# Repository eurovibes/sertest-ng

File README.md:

<!-- SPDX-FileCopyrightText: 2025 Benedikt Spranger <b.spranger@linutronix.de> -->
<!-- SPDX-License-Identifier: CERN-OHL-S-2.0 -->

# sertest-ng - A swiss knife serial testing tool

Serial interfaces like RS-232, RS-422/485 or CAN bus are even used in this
modern times. While reworking the 8250 driver in the Linux kernel jogness
faced plethora of nasty hardware dedication with modern serial hardware.
Single tasks overtop the banks in getting functional hardware. This sucks
and reliable full featured serial testing hardwaare is needed.

sertest-ng tries to fill that gap. It has a USB interface to control a
CAN/CAN-FD bus interface, a full featured RS-232 interface and a RS-422/485
interface. On top a RX/TX only RS-232 is equipped.

## License rules

sertest-ng is provided under the terms of the CERN-OHL-S license version 2 as
provided in the LICENSES/CERN-OHL-S-2.0 file.

Instead of adding license boilerplates to the individual files, sertest-ng uses
SPDX license identifiers, which are machine parseable and considered legaly
equivalent.

The SPDX license identifier in sertest-ng shall be added at the first possible
line in a file which can contain a comment. This is normally the first line
except for scripts. Scripts require the #!PATH_TO_INTERPRETER tag in the
first line; place the SPDX identifier into the second line.

The SPDX license identifier is added in form of a comment.

## Copyright and License
Copyright Benedikt Spranger 2025.
This source describes Open Hardware and is licensed under the CERNOHL-S v2.
You may redistribute and modify this source and make products using it
under the terms of the CERN-OHL-S v2
(https://ohwr.org/cern ohl_s_v2.txt).
This source is distributed WITHOUT ANY EXPRESS OR IMPLIED
WARRANTY, INCLUDING OF MERCHANTABILITY, SATISFACTORY
QUALITY AND FITNESS FOR A PARTICULAR PURPOSE. Please see
the CERN-OHL-S v2 for applicable conditions.
Source location: https://github.com/eurovibes/sertest-ng
As per CERN-OHL-S v2 section 4, should You produce hardware based
on this source, You must where practicable maintain the Source Location
visible on the external case of the sertest-ng or other products you make using
this source.

# Dedication
This hardware is dedicated to the great Linux Kernel Crew at Linutronix (https://www.linutronix.de)

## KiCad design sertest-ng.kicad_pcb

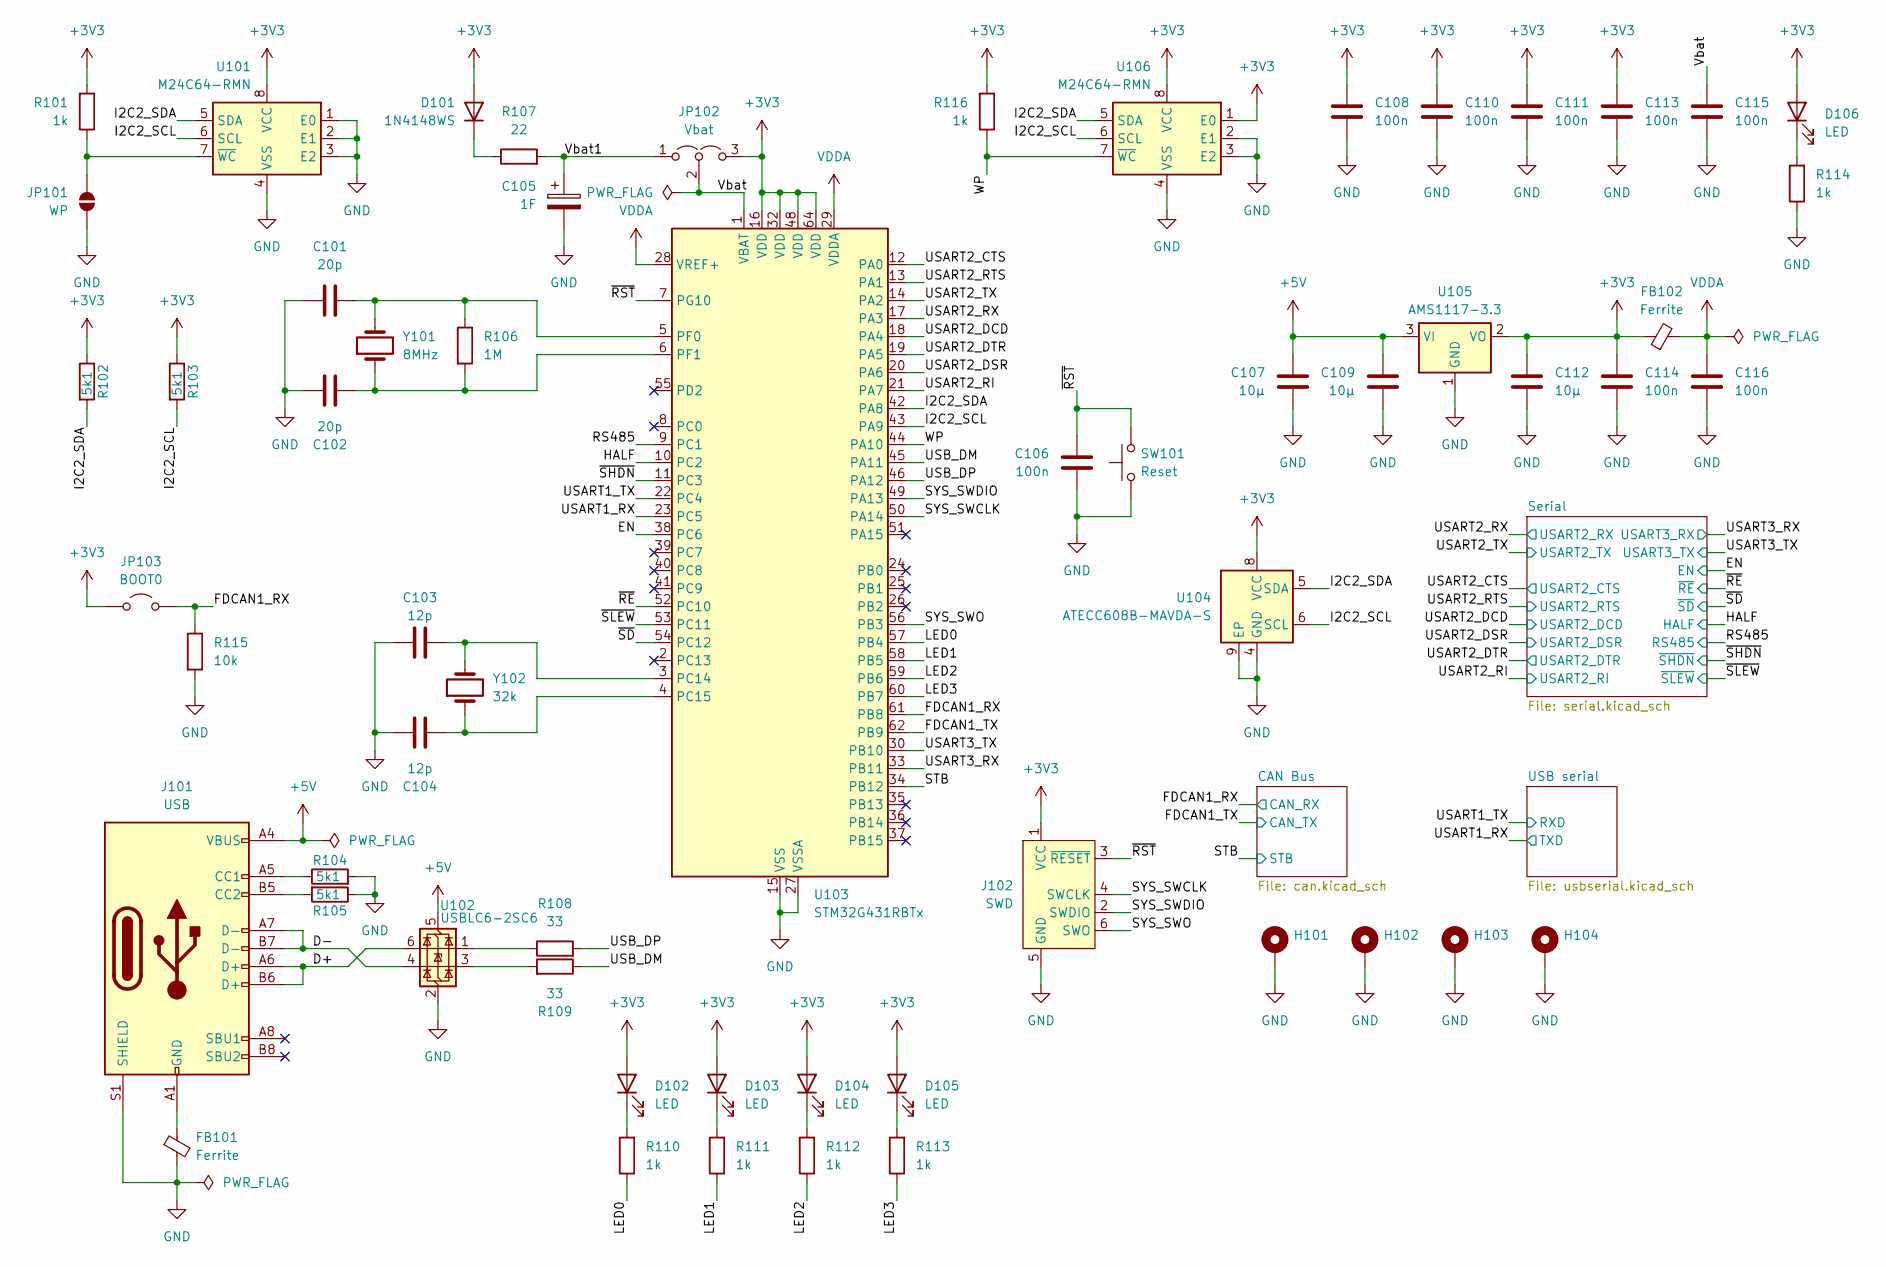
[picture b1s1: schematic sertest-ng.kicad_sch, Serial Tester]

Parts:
C101, C102: 20p; C_0402_1005Metric; lcsc# C1554
C103, C104: 12p; C_0402_1005Metric; lcsc# C1547
C105: 1F; CP_Radial_D8.0mm_P3.50mm
C106: 100n; C_0402_1005Metric; mpn CL05B104KB54PNC; LCSC# C307331
C107, C109, C112: 10µ; C_0805_2012Metric; lcsc# C15850
C108, C110, C111, C113, C114, C115, C116: 100n; C_0402_1005Metric; lcsc# C307331
D101: 1N4148WS; D_SOD-323; lcsc# C2128
D102, D103, D104, D105, D106: LED; LED_0603_1608Metric; mpn KT-0603R; LCSC# C2286
FB101: Ferrite; L_0805_2012Metric; mpn GZ1608D601TF; LCSC# C1002
FB102: Ferrite; L_0805_2012Metric; lcsc# C1015
H101, H102, H103, H104: MountingHole_3.2mm_M3_ISO14580_Pad; mpn N/A
J101: USB; USB_C_Receptacle_G-Switch_GT-USB-7010ASV; lcsc# C2988369
J102: SWD; Tag-Connect_TC2030-IDC-FP_2x03_P1.27mm_Vertical
JP101: WP; SolderJumper-2_P1.3mm_Open_Pad1.0x1.5mm
JP102: Vbat; SolderJumper-3_P1.3mm_Open_Pad1.0x1.5mm
JP103: BOOT0; SolderJumper-2_P1.3mm_Open_Pad1.0x1.5mm
R101, R110, R111, R112, R113, R114, R116: 1k; R_0402_1005Metric; mpn 0402WGF1001TCE; LCSC# C11702
R102, R103, R104, R105: 5k1; R_0402_1005Metric; lcsc# C25905
R106: 1M; R_0402_1005Metric; lcsc# C26083
R107: 22; R_1206_3216Metric; lcsc# C17958
R108, R109: 33; R_0402_1005Metric; lcsc# C25105
R115: 10k; R_0402_1005Metric; lcsc# C25744
SW101: Reset; SW_PUSH_6mm; mpn TACT-65R-F
U101, U106: M24C64-RMN; SOIC-8_3.9x4.9mm_P1.27mm; lcsc# C79988
U102: USBLC6-2SC6; SOT-23-6; mpn USBLC6-2SC6; LCSC# C2827654
U103: STM32G431RBTx; LQFP-64_10x10mm_P0.5mm; lcsc# C431633
U104: ATECC608B-MAVDA-S; DFN-8-1EP_3x2mm_P0.5mm_EP1.3x1.5mm; mpn ATECC608B-MAVDA-S; LCSC# C17350254
U105: AMS1117-3.3; SOT-223-3_TabPin2; lcsc# C6186
Y101: 8MHz; Crystal_SMD_5032-2Pin_5.0x3.2mm; lcsc# C115962
Y102: 32k; Crystal_SMD_3215-2Pin_3.2x1.5mm; lcsc# C32346

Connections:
+3V3: C108.1, C110.1, C111.1, C112.1, C113.1, C114.1, D101.2 (A), D102.2 (A), D103.2 (A), D104.2 (A), D105.2 (A), D106.2 (A), FB102.1, J102.1 (VCC), JP102.3 (B), JP103.1 (A), R101.2, R102.1, R103.1, R116.2, U101.8 (VCC), U103.16 (VDD), U103.32 (VDD), U103.48 (VDD), U103.64 (VDD), U104.8 (VCC), U105.2 (VO), U106.1 (E0), U106.8 (VCC); also elsewhere on the board
+5V: C107.1, C109.1, J101.A4 (VBUS), J101.A9 (VBUS), J101.B4 (VBUS), J101.B9 (VBUS), U102.5 (VBUS), U105.3 (VI)
/D+: J101.A6 (D+), J101.B6 (D+), U102.6 (I/O1)
/D-: J101.A7 (D-), J101.B7 (D-), U102.4 (I/O2)
/EN: U103.38 (PC6); also elsewhere on the board
/FDCAN1_RX: JP103.2 (B), R115.1, U103.61 (PB8); also elsewhere on the board
/FDCAN1_TX: U103.62 (PB9); also elsewhere on the board
/HALF: U103.10 (PC2); also elsewhere on the board
/I2C2_SCL: R103.2, U101.6 (SCL), U103.43 (PA9), U104.6 (SCL), U106.6 (SCL)
/I2C2_SDA: R102.2, U101.5 (SDA), U103.42 (PA8), U104.5 (SDA), U106.5 (SDA)
/LED0: R110.1, U103.57 (PB4)
/LED1: R111.1, U103.58 (PB5)
/LED2: R112.1, U103.59 (PB6)
/LED3: R113.1, U103.60 (PB7)
/RS485: U103.9 (PC1); also elsewhere on the board
/STB: U103.34 (PB12); also elsewhere on the board
/SYS_SWCLK: J102.4 (SWCLK), U103.50 (PA14)
/SYS_SWDIO: J102.2 (SWDIO), U103.49 (PA13)
/SYS_SWO: J102.6 (SWO), U103.56 (PB3)
/USART1_RX: U103.23 (PC5); also elsewhere on the board
/USART1_TX: U103.22 (PC4); also elsewhere on the board
/USART2_CTS: U103.12 (PA0); also elsewhere on the board
/USART2_DCD: U103.18 (PA4); also elsewhere on the board
/USART2_DSR: U103.20 (PA6); also elsewhere on the board
/USART2_DTR: U103.19 (PA5); also elsewhere on the board
/USART2_RI: U103.21 (PA7); also elsewhere on the board
/USART2_RTS: U103.13 (PA1); also elsewhere on the board
/USART2_RX: U103.17 (PA3); also elsewhere on the board
/USART2_TX: U103.14 (PA2); also elsewhere on the board
/USART3_RX: U103.33 (PB11); also elsewhere on the board
/USART3_TX: U103.30 (PB10); also elsewhere on the board
/USB_DM: R109.1, U103.45 (PA11)
/USB_DP: R108.2, U103.46 (PA12)
/Vbat: C115.1, JP102.2 (C), U103.1 (VBAT)
/Vbat1: C105.1, JP102.1 (A), R107.2
/WP: R116.1, U103.44 (PA10), U106.7 (~WC)
/~RE: U103.52 (PC10); also elsewhere on the board
/~RST: C106.1, J102.3 (~RESET), SW101.2, U103.7 (PG10)
/~SD: U103.54 (PC12); also elsewhere on the board
/~SHDN: U103.11 (PC3); also elsewhere on the board
/~SLEW: U103.53 (PC11); also elsewhere on the board
GND: C101.1, C102.1, C103.1, C104.1, C105.2, C106.2, C107.2, C108.2, C109.2, C110.2, C111.2, C112.2, C113.2, C114.2, C115.2, C116.2, FB101.2, H101.1, H102.1, H103.1, H104.1, J101.S1 (SHIELD), J102.5 (GND), JP101.1 (A), R104.2, R105.1, R114.1, R115.2, SW101.1, U101.1 (E0), U101.2 (E1), U101.3 (E2), U101.4 (VSS), U102.2 (GND), U103.15 (VSS), U103.27 (VSSA), U103.31 (VSS), U103.47 (VSS), U103.63 (VSS), U104.4 (GND), U104.9 (EP), U105.1 (GND), U106.2 (E1), U106.3 (E2), U106.4 (VSS); also elsewhere on the board
unnamed: D101.1 (K), R107.1
unnamed: D102.1 (K), R110.2
unnamed: D103.1 (K), R111.2
unnamed: D104.1 (K), R112.2
unnamed: D105.1 (K), R113.2
unnamed: D106.1 (K), R114.2
unnamed: FB101.1, J101.A1 (GND), J101.A12 (GND), J101.B1 (GND), J101.B12 (GND)
unnamed: J101.A5 (CC1), R104.1
unnamed: J101.B5 (CC2), R105.2
unnamed: JP101.2 (B), R101.1, U101.7 (~WC)
unnamed: R108.1, U102.1 (I/O1)
unnamed: R109.2, U102.3 (I/O2)
unnamed: C103.2, U103.3 (PC14), Y102.2
unnamed: C104.2, U103.4 (PC15), Y102.1
unnamed: C101.2, R106.1, U103.5 (PF0), Y101.2
unnamed: C102.2, R106.2, U103.6 (PF1), Y101.1
VDDA: C116.1, FB102.2, U103.28 (VREF+), U103.29 (VDDA)

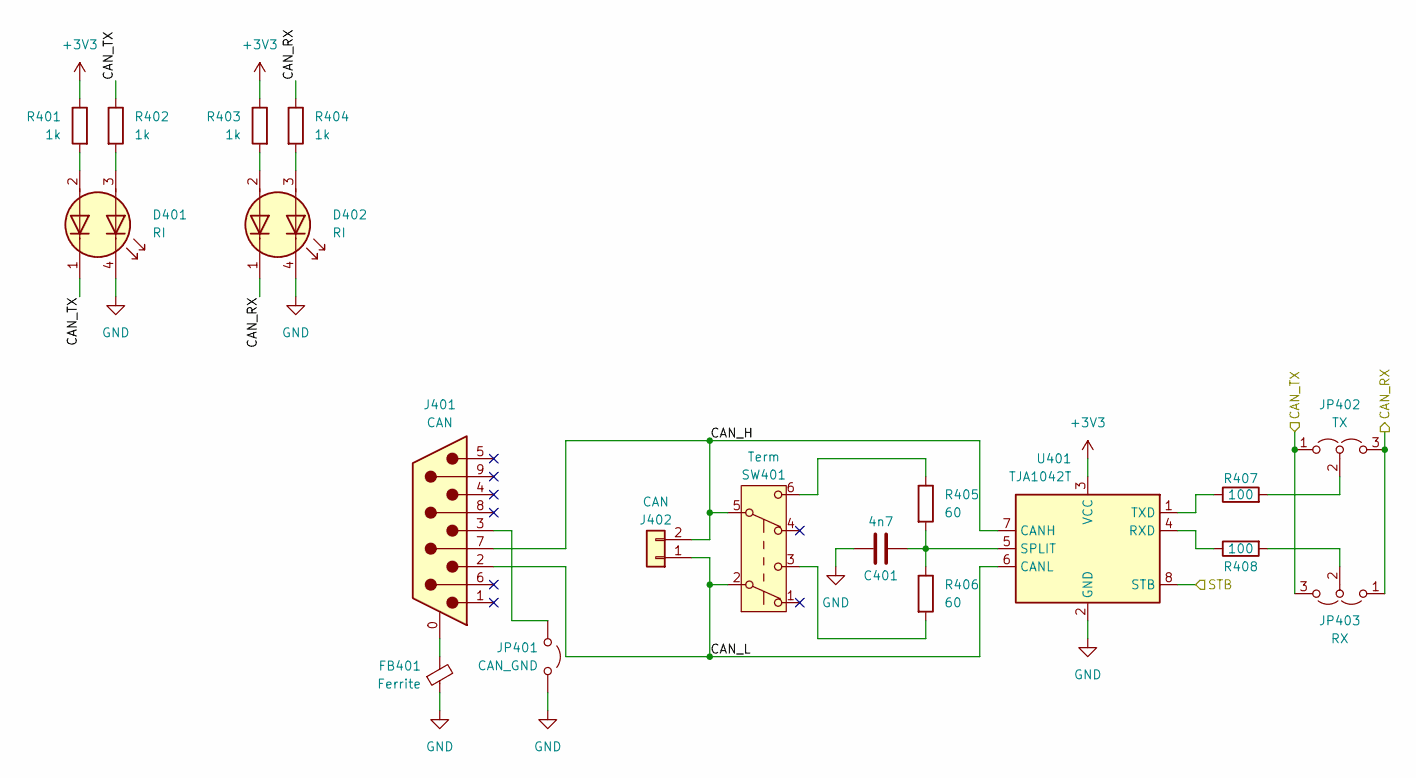
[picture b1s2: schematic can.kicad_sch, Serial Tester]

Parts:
C401: 4n7; C_0402_1005Metric; mpn 0402B472K500NT; LCSC# C1538
D401, D402: RI; LED_Kingbright_AAA3528ESGCT; lcsc# C601701
FB401: Ferrite; L_0805_2012Metric; lcsc# C1015
J401: CAN; DSUB-9_Pins_Horizontal_P2.77x2.84mm_EdgePinOffset4.94mm_Hou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
J402: CAN; TerminalBlock_WAGO_236-402_1x02_P5.00mm_45Degree; mpn 236-402; Digikey# 2946-236-402-ND
JP401: CAN_GND; PinHeader_1x02_P2.54mm_Vertical
JP402: TX; SolderJumper-3_P1.3mm_Open_Pad1.0x1.5mm
JP403: RX; SolderJumper-3_P1.3mm_Open_Pad1.0x1.5mm
R401, R402, R403, R404: 1k; R_0402_1005Metric; lcsc# C11702
R405, R406: 60; R_1206_3216Metric; mpn 1206W4F604JT5E; LCSC# C57572
R407, R408: 100; R_0402_1005Metric; mpn 0402WGF1000TCE; LCSC# C25076
SW401: Term; SW_Push_2P2T_Toggle_CK_PVA2xxH1xxxxxxV2; mpn TL2202EEZB (GRN ACT); Digikey# 141-TL2202EEZB(GRNACT)-ND
U401: TJA1042T; SOIC-8_3.9x4.9mm_P1.27mm; mpn TJA1042T/1J; LCSC# C53670

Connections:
+3V3: R401.1, R403.1, U401.3 (VCC); also elsewhere on the board
/CAN Bus/CAN_H: J401.7, J402.2, SW401.5 (B), U401.7 (CANH)
/CAN Bus/CAN_L: J401.2, J402.1, SW401.2 (B), U401.6 (CANL)
/FDCAN1_RX: D402.1 (K2), JP402.3 (B), JP403.1 (A), R404.1; also elsewhere on the board
/FDCAN1_TX: D401.1 (K2), JP402.1 (A), JP403.3 (B), R402.1; also elsewhere on the board
/STB: U401.8 (STB); also elsewhere on the board
GND: C401.1, D401.4 (K1), D402.4 (K1), FB401.1, JP401.1 (A), U401.2 (GND); also elsewhere on the board
unnamed: D401.3 (A1), R402.2
unnamed: D401.2 (A2), R401.2
unnamed: D402.3 (A1), R404.2
unnamed: D402.2 (A2), R403.2
unnamed: FB401.2, J401.0 (PAD)
unnamed: J401.3, JP401.2 (B)
unnamed: JP402.2 (C), R407.2
unnamed: JP403.2 (C), R408.2
unnamed: R405.1, SW401.6 (C)
unnamed: R406.2, SW401.3 (C)
unnamed: R408.1, U401.4 (RXD)
unnamed: C401.2, R405.2, R406.1, U401.5 (SPLIT)
unnamed: R407.1, U401.1 (TXD)

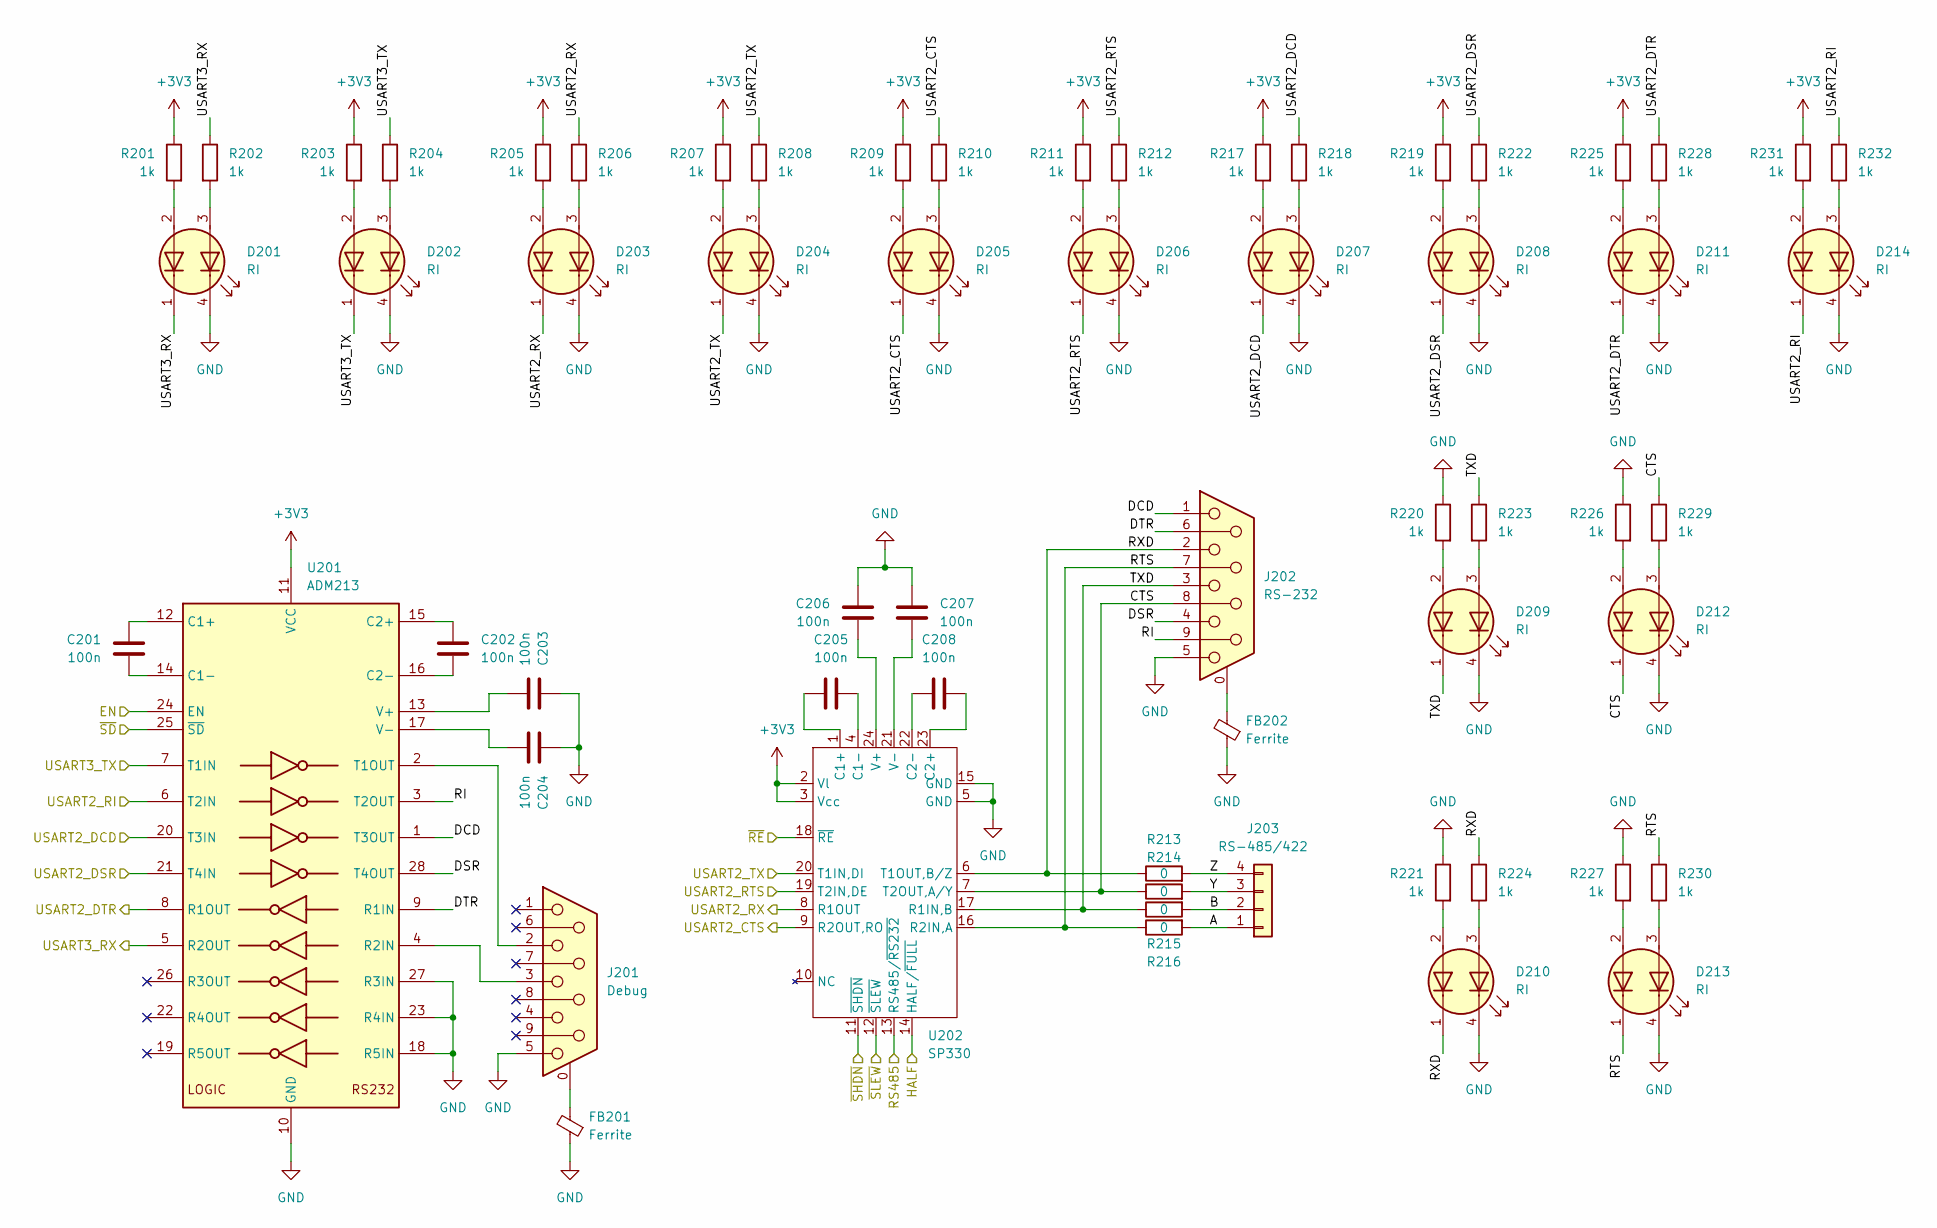
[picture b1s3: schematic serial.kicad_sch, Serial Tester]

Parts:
C201, C202, C203, C204, C205, C206, C207, C208: 100n; C_0402_1005Metric; lcsc# C307331
D201, D202, D203, D204, D205, D206, D207, D208, D209, D210, D211, D212, D213, D214: RI; LED_Kingbright_AAA3528ESGCT; lcsc# C601701
FB201, FB202: Ferrite; L_0805_2012Metric; lcsc# C1015
J201: Debug; DSUB-9_Socket_Horizontal_P2.77x2.84mm_EdgePinOffset4.94mm_H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
J202: RS-232; DSUB-9_Socket_Horizontal_P2.77x2.84mm_EdgePinOffset4.94mm_H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
J203: RS-485/422; TerminalBlock_WAGO_236-404_1x04_P5.00mm_45Degree
R201, R202, R203, R204, R205, R206, R207, R208, R209, R210, R211, R212, R217, R218, R219, R220, R221, R222, R223, R224, R225, R226, R227, R228, R229, R230, R231, R232: 1k; R_0402_1005Metric; lcsc# C11702
R213, R214, R215, R216: 0; R_0402_1005Metric; lcsc# C17168
U201: ADM213; SSOP-28_5.3x10.2mm_P0.65mm; lcsc# C415725
U202: SP330; TSSOP-24_4.4x7.8mm_P0.65mm; lcsc# C916084

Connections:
+3V3: R201.1, R203.1, R205.1, R207.1, R209.1, R211.1, R217.1, R219.1, R225.1, R231.1, U201.11 (VCC), U202.2 (Vl), U202.3 (Vcc); also elsewhere on the board
/EN: U201.24 (EN); also elsewhere on the board
/HALF: U202.14 (HALF/~FULL); also elsewhere on the board
/RS485: U202.13 (RS485/~RS232); also elsewhere on the board
/Serial/A: J203.1, R216.2
/Serial/B: J203.2, R215.2
/Serial/CTS: D212.1 (K2), J202.8, R214.1, R229.1, U202.7 (T2OUT,A/Y)
/Serial/DCD: J202.1, U201.1 (T3OUT)
/Serial/DSR: J202.4, U201.28 (T4OUT)
/Serial/DTR: J202.6, U201.9 (R1IN)
/Serial/RI: J202.9, U201.3 (T2OUT)
/Serial/RTS: D213.1 (K2), J202.7, R216.1, R230.1, U202.16 (R2IN,A)
/Serial/RXD: D210.1 (K2), J202.2, R213.1, R224.1, U202.6 (T1OUT,B/Z)
/Serial/TXD: D209.1 (K2), J202.3, R215.1, R223.1, U202.17 (R1IN,B)
/Serial/Y: J203.3, R214.2
/Serial/Z: J203.4, R213.2
/USART2_CTS: D205.1 (K2), R210.1, U202.9 (R2OUT,RO); also elsewhere on the board
/USART2_DCD: D207.1 (K2), R218.1, U201.20 (T3IN); also elsewhere on the board
/USART2_DSR: D208.1 (K2), R222.1, U201.21 (T4IN); also elsewhere on the board
/USART2_DTR: D211.1 (K2), R228.1, U201.8 (R1OUT); also elsewhere on the board
/USART2_RI: D214.1 (K2), R232.1, U201.6 (T2IN); also elsewhere on the board
/USART2_RTS: D206.1 (K2), R212.1, U202.19 (T2IN,DE); also elsewhere on the board
/USART2_RX: D203.1 (K2), R206.1, U202.8 (R1OUT); also elsewhere on the board
/USART2_TX: D204.1 (K2), R208.1, U202.20 (T1IN,DI); also elsewhere on the board
/USART3_RX: D201.1 (K2), R202.1, U201.5 (R2OUT); also elsewhere on the board
/USART3_TX: D202.1 (K2), R204.1, U201.7 (T1IN); also elsewhere on the board
/~RE: U202.18 (~RE); also elsewhere on the board
/~SD: U201.25 (~SD); also elsewhere on the board
/~SHDN: U202.11 (~SHDN); also elsewhere on the board
/~SLEW: U202.12 (~SLEW); also elsewhere on the board
GND: C203.2, C204.2, C206.2, C207.2, D201.4 (K1), D202.4 (K1), D203.4 (K1), D204.4 (K1), D205.4 (K1), D206.4 (K1), D207.4 (K1), D208.4 (K1), D209.4 (K1), D210.4 (K1), D211.4 (K1), D212.4 (K1), D213.4 (K1), D214.4 (K1), FB201.1, FB202.1, J201.5, J202.5, R220.1, R221.1, R226.1, R227.1, U201.10 (GND), U201.18 (R5IN), U201.23 (R4IN), U201.27 (R3IN), U202.5 (GND), U202.15 (GND); also elsewhere on the board
unnamed: D201.3 (A1), R202.2
unnamed: D201.2 (A2), R201.2
unnamed: D202.3 (A1), R204.2
unnamed: D202.2 (A2), R203.2
unnamed: D203.3 (A1), R206.2
unnamed: D203.2 (A2), R205.2
unnamed: D204.3 (A1), R208.2
unnamed: D204.2 (A2), R207.2
unnamed: D205.3 (A1), R210.2
unnamed: D205.2 (A2), R209.2
unnamed: D206.3 (A1), R212.2
unnamed: D206.2 (A2), R211.2
unnamed: D207.3 (A1), R218.2
unnamed: D207.2 (A2), R217.2
unnamed: D208.3 (A1), R222.2
unnamed: D208.2 (A2), R219.2
unnamed: D209.3 (A1), R223.2
unnamed: D209.2 (A2), R220.2
unnamed: D210.3 (A1), R224.2
unnamed: D210.2 (A2), R221.2
unnamed: D211.3 (A1), R228.2
unnamed: D211.2 (A2), R225.2
unnamed: D212.3 (A1), R229.2
unnamed: D212.2 (A2), R226.2
unnamed: D213.3 (A1), R230.2
unnamed: D213.2 (A2), R227.2
unnamed: D214.3 (A1), R232.2
unnamed: D214.2 (A2), R231.2
unnamed: FB201.2, J201.0 (PAD)
unnamed: FB202.2, J202.0 (PAD)
unnamed: C201.2, U201.12 (C1+)
unnamed: C201.1, U201.14 (C1-)
unnamed: C202.2, U201.15 (C2+)
unnamed: C202.1, U201.16 (C2-)
unnamed: J201.3, U201.4 (R2IN)
unnamed: J201.2, U201.2 (T1OUT)
unnamed: C203.1, U201.13 (V+)
unnamed: C204.1, U201.17 (V-)
unnamed: C205.1, U202.1 (C1+)
unnamed: C205.2, U202.4 (C1-)
unnamed: C208.2, U202.23 (C2+)
unnamed: C208.1, U202.22 (C2-)
unnamed: C206.1, U202.24 (V+)
unnamed: C207.1, U202.21 (V-)

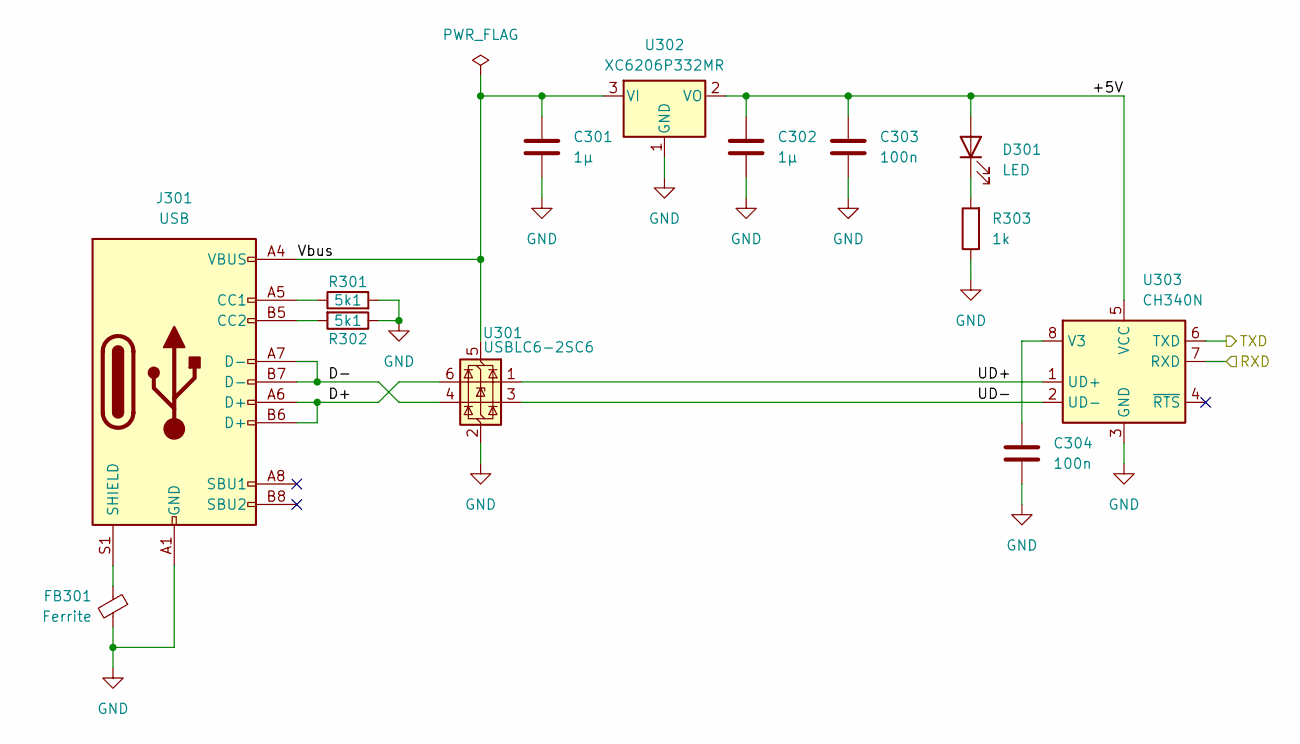
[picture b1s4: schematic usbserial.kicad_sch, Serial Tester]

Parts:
C301, C302: 1µ; C_0603_1608Metric; mpn CL10A105KB8NNNC; LCSC# C15849
C303, C304: 100n; C_0402_1005Metric; mpn CL05B104KB54PNC; LCSC# C307331
D301: LED; LED_0603_1608Metric; mpn KT-0603R; LCSC# C2286
FB301: Ferrite; L_0805_2012Metric; mpn GZ1608D601TF; LCSC# C1002
J301: USB; USB_C_Receptacle_G-Switch_GT-USB-7010ASV; lcsc# C2988369
R301, R302: 5k1; R_0402_1005Metric; lcsc# C25905
R303: 1k; R_0402_1005Metric; mpn 0402WGF1001TCE; LCSC# C11702
U301: USBLC6-2SC6; SOT-23-6; mpn USBLC6-2SC6; LCSC# C2827654
U302: XC6206P332MR; SOT-23-3; mpn XC6206P332MR-G; LCSC# C5446
U303: CH340N; JEITA_SOIC-8_3.9x4.9mm_P1.27mm; mpn CH340N; LCSC# C2977777

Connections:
/USART1_RX: U303.6 (TXD); also elsewhere on the board
/USART1_TX: U303.7 (RXD); also elsewhere on the board
/USB serial/+5V: C302.1, C303.1, D301.2 (A), U302.2 (VO), U303.5 (VCC)
/USB serial/D+: J301.A6 (D+), J301.B6 (D+), U301.6 (I/O1)
/USB serial/D-: J301.A7 (D-), J301.B7 (D-), U301.4 (I/O2)
/USB serial/UD+: U301.1 (I/O1), U303.1 (UD+)
/USB serial/UD-: U301.3 (I/O2), U303.2 (UD-)
/USB serial/Vbus: C301.1, J301.A4 (VBUS), J301.A9 (VBUS), J301.B4 (VBUS), J301.B9 (VBUS), U301.5 (VBUS), U302.3 (VI)
GND: C301.2, C302.2, C303.2, C304.2, FB301.2, J301.A1 (GND), J301.A12 (GND), J301.B1 (GND), J301.B12 (GND), R301.2, R302.1, R303.1, U301.2 (GND), U302.1 (GND), U303.3 (GND); also elsewhere on the board
unnamed: D301.1 (K), R303.2
unnamed: J301.A5 (CC1), R301.1
unnamed: J301.B5 (CC2), R302.2
unnamed: FB301.1, J301.S1 (SHIELD)
unnamed: C304.1, U303.8 (V3)

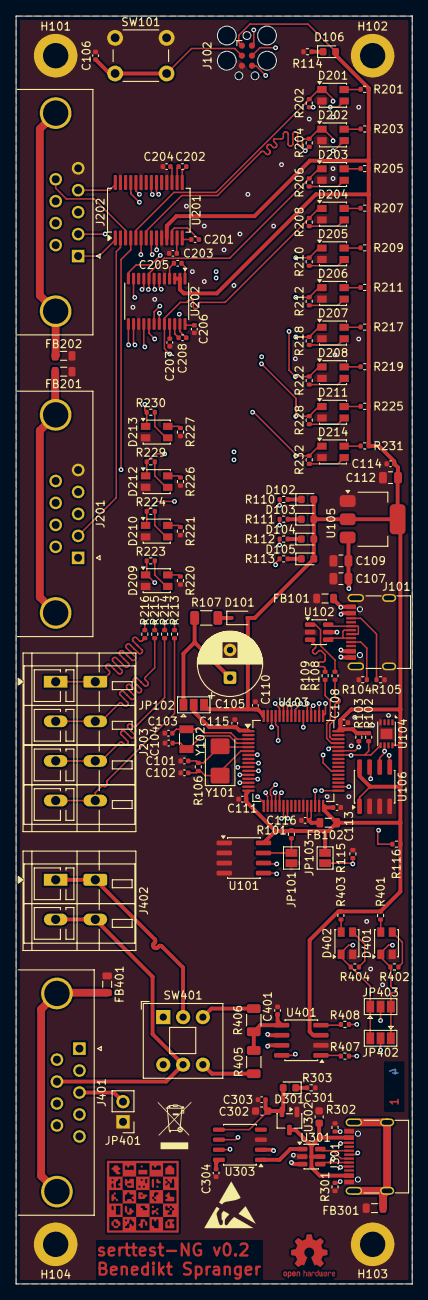
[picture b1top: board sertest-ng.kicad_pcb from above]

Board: 4 copper layers, 50.0 x 160.0 mm, 151 parts (0 on the bottom side), 141 nets.

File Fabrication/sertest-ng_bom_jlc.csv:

"Comment","Designator","Footprint","LCSC Part #"
"12p","C103,C104","C_0402_1005Metric","C1547"
"20p","C101,C102","C_0402_1005Metric","C1554"
"4n7","C401","C_0402_1005Metric","C1538"
"100n","C106,C108,C110,C111,C113,C114,C115,C116,C201,C202,C203,C204,C205,C206,C207,C208,C303,C304","C_0402_1005Metric","C307331"
"1µ","C301,C302","C_0603_1608Metric","C15849"
"10µ","C107,C109,C112","C_0805_2012Metric","C15850"
"1N4148WS","D101","D_SOD-323","C2128"
"LED","D102,D103,D104,D105,D106,D301","LED_0603_1608Metric","C2286"
"RI","D201,D202,D203,D204,D205,D206,D207,D208,D209,D210,D211,D212,D213,D214,D401,D402","LED_Kingbright_AAA3528ESGCT","C601701"
"Ferrite","FB101,FB102,FB201,FB202,FB301,FB401","L_0805_2012Metric","C1002 C1015"
"USB","J101,J301","USB_C_Receptacle_G-Switch_GT-USB-7010ASV","C2988369"
"0","R213,R214,R215,R216","R_0402_1005Metric","C17168"
"22","R107","R_1206_3216Metric","C17958"
"33","R108,R109","R_0402_1005Metric","C25105"
"60","R405,R406","R_1206_3216Metric","C57572"
"100","R407,R408","R_0402_1005Metric","C25076"
"1k","R101,R110,R111,R112,R113,R114,R116,R201,R202,R203,R204,R205,R206,R207,R208,R209,R210,R211,R212,R217,R218,R219,R220,R221,R222,R223,R224,R225,R226,R227,R228,R229,R230,R231,R232,R303,R401,R402,R403,R404","R_0402_1005Metric","C11702"
"5k1","R102,R103,R104,R105,R301,R302","R_0402_1005Metric","C25905"
"10k","R115","R_0402_1005Metric","C25744"
"1M","R106","R_0402_1005Metric","C26083"
"ADM213","U201","SSOP-28_5.3x10.2mm_P0.65mm","C415725"
"AMS1117-3.3","U105","SOT-223-3_TabPin2","C6186"
"ATECC608B-MAVDA-S","U104","DFN-8-1EP_3x2mm_P0.5mm_EP1.3x1.5mm","C17350254 C17561150"
"CH340N","U303","JEITA_SOIC-8_3.9x4.9mm_P1.27mm","C2977777 C5446"
"M24C64-RMN","U101,U106","SOIC-8_3.9x4.9mm_P1.27mm","C79988"
"SP330","U202","TSSOP-24_4.4x7.8mm_P0.65mm","C916084"
"STM32G431RBTx","U103","LQFP-64_10x10mm_P0.5mm","C431633"
"TJA1042T","U401","SOIC-8_3.9x4.9mm_P1.27mm","C53670"
"USBLC6-2SC6","U102,U301","SOT-23-6","C2827654 C2687116"
"XC6206P332MR","U302","SOT-23-3","C5446 C2977777"
"32k","Y102","Crystal_SMD_3215-2Pin_3.2x1.5mm","C32346"
"8MHz","Y101","Crystal_SMD_5032-2Pin_5.0x3.2mm","C115962"

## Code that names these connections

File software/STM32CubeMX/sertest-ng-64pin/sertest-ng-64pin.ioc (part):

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Mcu.Name=STM32G431R(6-8-B)Tx
Mcu.Package=LQFP64
Mcu.UserName=STM32G431RBTx
PA0.Mode=CTS_RTS
PA0.Signal=USART2_CTS
PA1.Mode=CTS_RTS
PA1.Signal=USART2_RTS
PA11.Mode=Device
PA11.Signal=USB_DM
PA12.Mode=Device
PA12.Signal=USB_DP
PA13.Mode=Trace_Asynchronous_SW
PA13.Signal=SYS_JTMS-SWDIO
PA14.Mode=Trace_Asynchronous_SW
PA14.Signal=SYS_JTCK-SWCLK
PA2.Mode=Asynchronous
PA2.Signal=USART2_TX
PA3.Mode=Asynchronous
PA3.Signal=USART2_RX
PA4.GPIOParameters=GPIO_Label
PA4.GPIO_Label=USART2_DCD
PA4.Signal=GPIO_Output
PA5.GPIOParameters=GPIO_Label
PA5.GPIO_Label=USART2_DTR
PA5.Signal=GPIO_Input
PA6.GPIOParameters=GPIO_Label
PA6.GPIO_Label=USART2_DSR
PA6.Signal=GPIO_Output
PA7.GPIOParameters=GPIO_Label
PA7.GPIO_Label=USART2_RI
PA7.Signal=GPIO_Output
PA8.Mode=I2C
PA8.Signal=I2C2_SDA
PA9.Mode=I2C
PA9.Signal=I2C2_SCL
PB10.Mode=Asynchronous
PB10.Signal=USART3_TX
PB11.Mode=Asynchronous
PB11.Signal=USART3_RX
PB12.GPIOParameters=GPIO_Label
PB12.GPIO_Label=STB
PB12.Signal=GPIO_Output
PB3.Mode=Trace_Asynchronous_SW
PB3.Signal=SYS_JTDO-SWO
PB4.GPIOParameters=GPIO_Label
PB4.GPIO_Label=LED0
PB4.Signal=GPIO_Output
PB5.GPIOParameters=GPIO_Label
PB5.GPIO_Label=LED1
PB5.Signal=GPIO_Output
PB6.GPIOParameters=GPIO_Label
PB6.GPIO_Label=LED2
PB6.Signal=GPIO_Output
PB7.GPIOParameters=GPIO_Label
PB7.GPIO_Label=LED3
PB7.Signal=GPIO_Output
PB8-BOOT0.Mode=FDCAN_Activate
PB8-BOOT0.Signal=FDCAN1_RX
PB9.Mode=FDCAN_Activate
PB9.Signal=FDCAN1_TX
PC1.GPIOParameters=GPIO_Label
PC1.GPIO_Label=RS485
PC1.Signal=GPIO_Output
PC10.GPIOParameters=GPIO_Label
PC10.GPIO_Label=nRE
PC10.Signal=GPIO_Output
PC11.GPIOParameters=GPIO_Label
PC11.GPIO_Label=nSLEW
PC11.Signal=GPIO_Output
PC12.GPIOParameters=GPIO_Label
PC12.GPIO_Label=nSD
PC12.Signal=GPIO_Output
PC14-OSC32_IN.Mode=LSE-External-Oscillator
PC14-OSC32_IN.Signal=RCC_OSC32_IN
PC15-OSC32_OUT.Mode=LSE-External-Oscillator
PC15-OSC32_OUT.Signal=RCC_OSC32_OUT
PC2.GPIOParameters=GPIO_Label
PC2.GPIO_Label=HALF
PC2.Signal=GPIO_Output
PC3.GPIOParameters=GPIO_Label
PC3.GPIO_Label=nSHDN
PC3.Signal=GPIO_Output
PC4.Mode=Asynchronous
PC4.Signal=USART1_TX
PC5.Mode=Asynchronous
PC5.Signal=USART1_RX
PC6.GPIOParameters=GPIO_Label
PC6.GPIO_Label=EN
PC6.Signal=GPIO_Output
PF0-OSC_IN.Mode=HSE-External-Oscillator
PF0-OSC_IN.Signal=RCC_OSC_IN
PF1-OSC_OUT.Mode=HSE-External-Oscillator
PF1-OSC_OUT.Signal=RCC_OSC_OUT
RCC.HSE_VALUE=8000000
RCC.SYSCLKFreq_VALUE=168000000
RCC.SYSCLKSource=RCC_SYSCLKSOURCE_PLLCLK
board=custom

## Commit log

2026-01-24 Add logo
2026-01-24 Add github actions
2026-01-24 Revisit 3D models
2026-01-24 Initial
2026-01-24 Initial gh-pages commit
2026-01-24 Deploying to gh-pages from @ eurovibes/sertest-ng@9840af897d8b0a98e2bcef5af7633110423ef0b0 🚀
2026-01-26 Deploying to gh-pages from @ eurovibes/sertest-ng@d87ae5931d802483cd956921e99df2dbb285ed76 🚀
2026-01-26 Fix Dual LED footprint issue
2026-01-26 Deploying to gh-pages from @ eurovibes/sertest-ng@e03f8e5e6108b18d4856317c03eadad0703cad57 🚀
2026-01-27 Replace JLCPCB part to fit footprint
2026-01-27 Deploying to gh-pages from @ eurovibes/sertest-ng@0dc5bc12d7f59b25ef8eb838ef244f0670082cc1 🚀
2026-01-31 Add enclosure
2026-03-03 Deploying to gh-pages from @ eurovibes/sertest-ng@2991ba3118ce12d7d1ee4fa3d16469fd546db771 🚀
2026-03-14 Deploying to gh-pages from @ eurovibes/sertest-ng@fd12f7b8a575bdaec5f4aed8c1687597aec7e080 🚀
2026-03-16 Update STM32CubeMX project
2026-03-16 Rework serial from DTE to DCE
2026-03-16 Swap USART1 RX/TX
2026-03-16 Fix USB signal swap
2026-03-16 Add USB termination resistors
2026-03-16 Add BOOT0 support
2026-03-21 Add second EEPROM
2026-03-21 Add JFlash configuration
2026-03-21 Deploying to gh-pages from @ eurovibes/sertest-ng@5159d4b81fca0939de04461b6e2f5ac2f631fdfa 🚀
2026-03-22 Initial Zephyr application
2026-03-22 Bump to v0.2
2026-03-22 Deploying to gh-pages from @ eurovibes/sertest-ng@28a13e848e09c40d7e9fa2b801b2ebcab0b7b692 🚀
2026-03-31 Add USB CAN interface
2026-03-31 More cryptolib stuff
2026-04-01 zephyr: Switch to devel/sertest-ng
2026-04-01 Action: Build Zephyr firmware
2026-04-02 Actions: update actions
2026-04-02 Deploying to gh-pages from @ eurovibes/sertest-ng@1c60f4aff8c6af842e4c22cd60a319713d98fdc1 🚀

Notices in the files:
can.kicad_sch:
This work is licensed under the CERN-OHL-S v2
